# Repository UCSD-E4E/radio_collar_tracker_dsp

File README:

radio_collar_tracker_drone
====================
Airborne Wildlife Radio Collar Tracker - UAS Component

Engineers for Exploration, UCSD Project

Installing the payload software
===============================
1.	Install the required dependencies
	1.	python
	2.	pynmea2
		1.	`pip install pynmea2`
	3.  pyserial
		1.  `sudo apt-get install python-serial`
	4.	libusb-1.0-0-dev
	3.	rtl-sdr
		1.	`git clone https://github.com/steve-m/librtlsdr`
		2.	`mkdir librtlsdr/build`
		3.	`cd librtlsddr/build`
		4.	`sudo cmake ../ -DINSTALL_UDEV_RULES=ON -DDETACH_KERNEL_DRIVER=ON`
		5.	`make`
		6.	`sudo make install`
		7.	`ldconfig`
2.	Install the software
	1.	`cd <radio_collar_tracker_drone>`
	2.  `./autogen.sh`
	3.  `./configure`
	4.	`make`
	5.	`sudo make install`

Running the payload software (standalone)
=========================================
`rctstart`

#Running the payload software (hardware-based initialization)
##Payload Power On Procedure
1.	Disconnect power to AUTOPILOT, PAYLOD
2.	Connect power to PAYLOAD
3.	Connect power to AUTOPILOT
4.	Flip PAYLOAD SWITCH to the ON position.
5.	Wait for the PAYLOAD STATUS LIGHT to turn green for at least 10 seconds.
6.	Flip PAYLOAD SWITCH to the OFF position.
7.	Wait for the PAYLOAD STATUS LIGHT to turn off within 5 seconds.
8.	Connect the GROUND CONTROL STATION to the AUTOPILOT.
9.	Payload Power On Procedure complete.

## Payload Start Procedure
1.	Complete the Payload Power On Procedure.
2.	Flip PAYLOAD SWITCH to the ON position.
3.	Wait for the PAYLOAD STATUS LIGHT to turn green for at least 10 seconds.
4.	Payload Start Procedure complete.

## Payload Stop Procedure
1.	Flip PAYLOAD SWITCH to the OFF position.
2.	Wait for the PAYLOAD STATUS LIGHT to turn off within 5 seconds.
3.	Payload Stop Procedure complete.

## Payload Power Off Procedure
1.	Complete the Payload Stop Procedure.
2.	Disconnect power to the PAYLOAD.
3.	Payload Power Off Procedure complete.

Output Data Format
==================
Output data is located in `/home/pi/rct/`.  Each run consists of a number of IQ
(raw) data files, GPS data files, and a metadata file.  The name format for each
type of file is `[type]_[run]_[file_num]`.  The `type` field specifies, in
capital letters, the type of file (i.e. RAW_DATA, GPS, or META).  The `run`
field specifies a numerical identifier for each run, assigned sequentially.
This field is always 6 characters wide, zero padded.  The `file_num` field
specifies the ordering of the IQ data files.  The first file recorded would have
a file number of 1, sequential files having sequential numbers.  This field is
always 6 characters wide, zero padded.

The raw data files contain the raw IQ data recorded as pairs of 8-bit unsigned
integers.  Each pair represents the in-phase and quadrature components of the
recorded signal in sequence.  See
https://en.wikipedia.org/wiki/In-phase_and_quadrature_components for an
explanation of IQ signal representation.  Each file contains at most 10485760
samples, or 5.12 seconds of data.  IQ data is recorded at 2.048 MSps.

The GPS data files contain timestamped snapshots of autopilot telemetry.  Fields
are comma separated, and are: local capture time (UTC in seconds), lat (degrees
\* 1e7), lon (degrees * 1e7), time since autopilot boot (ms), absolute altitude
(meters MSL), relative altitude (meters AGL), x axis velocity (m/s), y axis
velocity (m/s), z axis velocity (m/s), heading (degrees).  Note: I do not know
whether the heading is relative to true north or magnetic north.  The NED frame
ideally is relative to true north, but I don't know if the heading is reported
before or after declination offsets are taken into account.

The metadata file contains metadata pertaining to the configuration of the
payload.  Each line contains one field.  The key for each field is followed by a
colon, then the value for that field, followed by a newline character:
```
[field_name]: [field_value]
```
The whitespace between the colon and field value is optional, and preferred for
readability, but cannot be a newline.  The metadata file contains the following
fields: local IQ data start time (UTC in seconds), SDR center frequency (Hz),
SDR sampling frequency (Hz), SDR gain (dB).

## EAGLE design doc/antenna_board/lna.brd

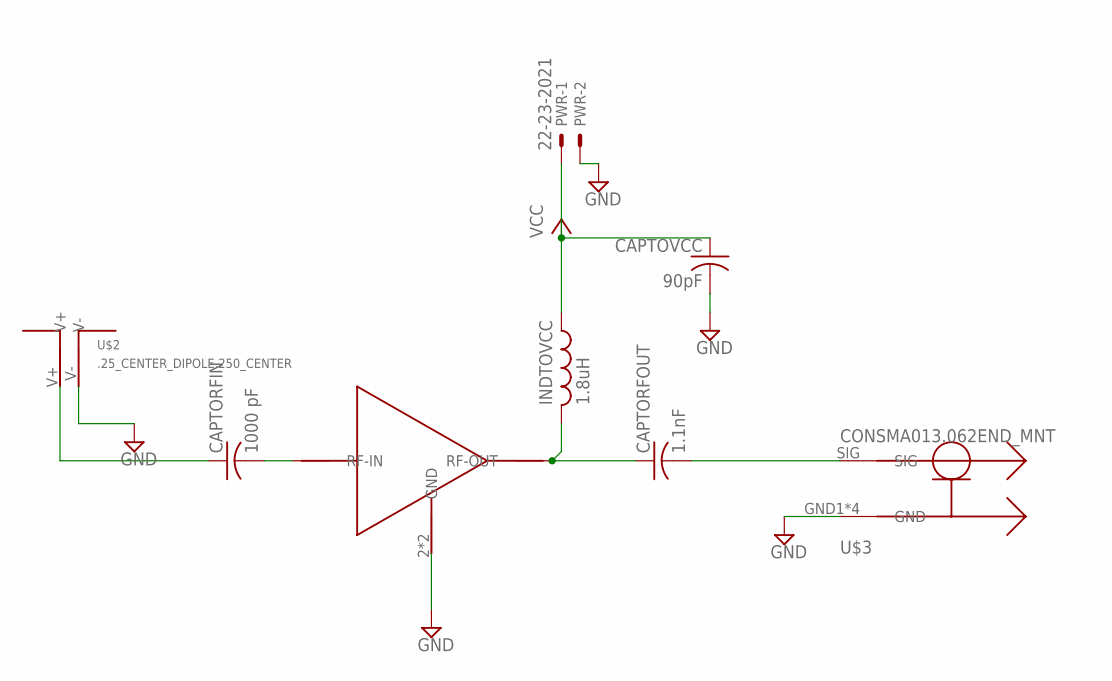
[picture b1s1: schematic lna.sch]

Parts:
CAPTORFIN: 1000 pF; C0603
CAPTORFOUT: 1.1nF; C0603
CAPTOVCC: 90pF; C0603
INDTOVCC: 1.8uH; L2012C
PWR: 22-23-2021
U$1: PSA4-5043+
U$2: .25_CENTER_DIPOLE.250_CENTER; .25_SPACING
U$3: CONSMA013.062END_MNT; SMA_EDGE_MNT

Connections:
GND: CAPTOVCC.2, PWR.2, U$1.2 (GND), U$1.4 (GND), U$2.V-, U$3.GND1 (GND), U$3.GND2 (GND), U$3.GND3 (GND), U$3.GND4 (GND)
unnamed: CAPTORFIN.1, U$2.V+
unnamed: CAPTORFOUT.1, INDTOVCC.2, U$1.1 (RF-OUT)
unnamed: CAPTORFOUT.2, U$3.SIG
unnamed: CAPTORFIN.2, U$1.3 (RF-IN)
VCC: CAPTOVCC.1, INDTOVCC.1, PWR.1

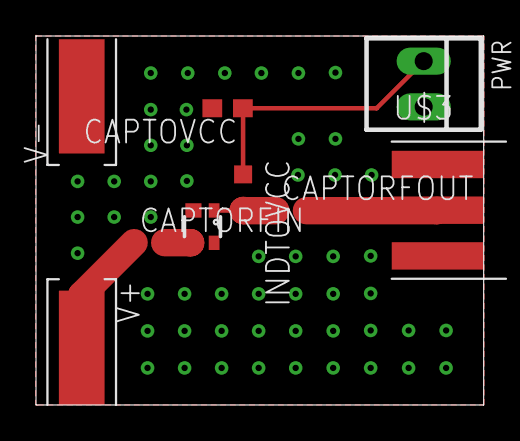
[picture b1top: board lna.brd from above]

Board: 2 copper layers, 24.9 x 20.5 mm, 8 parts (0 on the bottom side), 6 nets.

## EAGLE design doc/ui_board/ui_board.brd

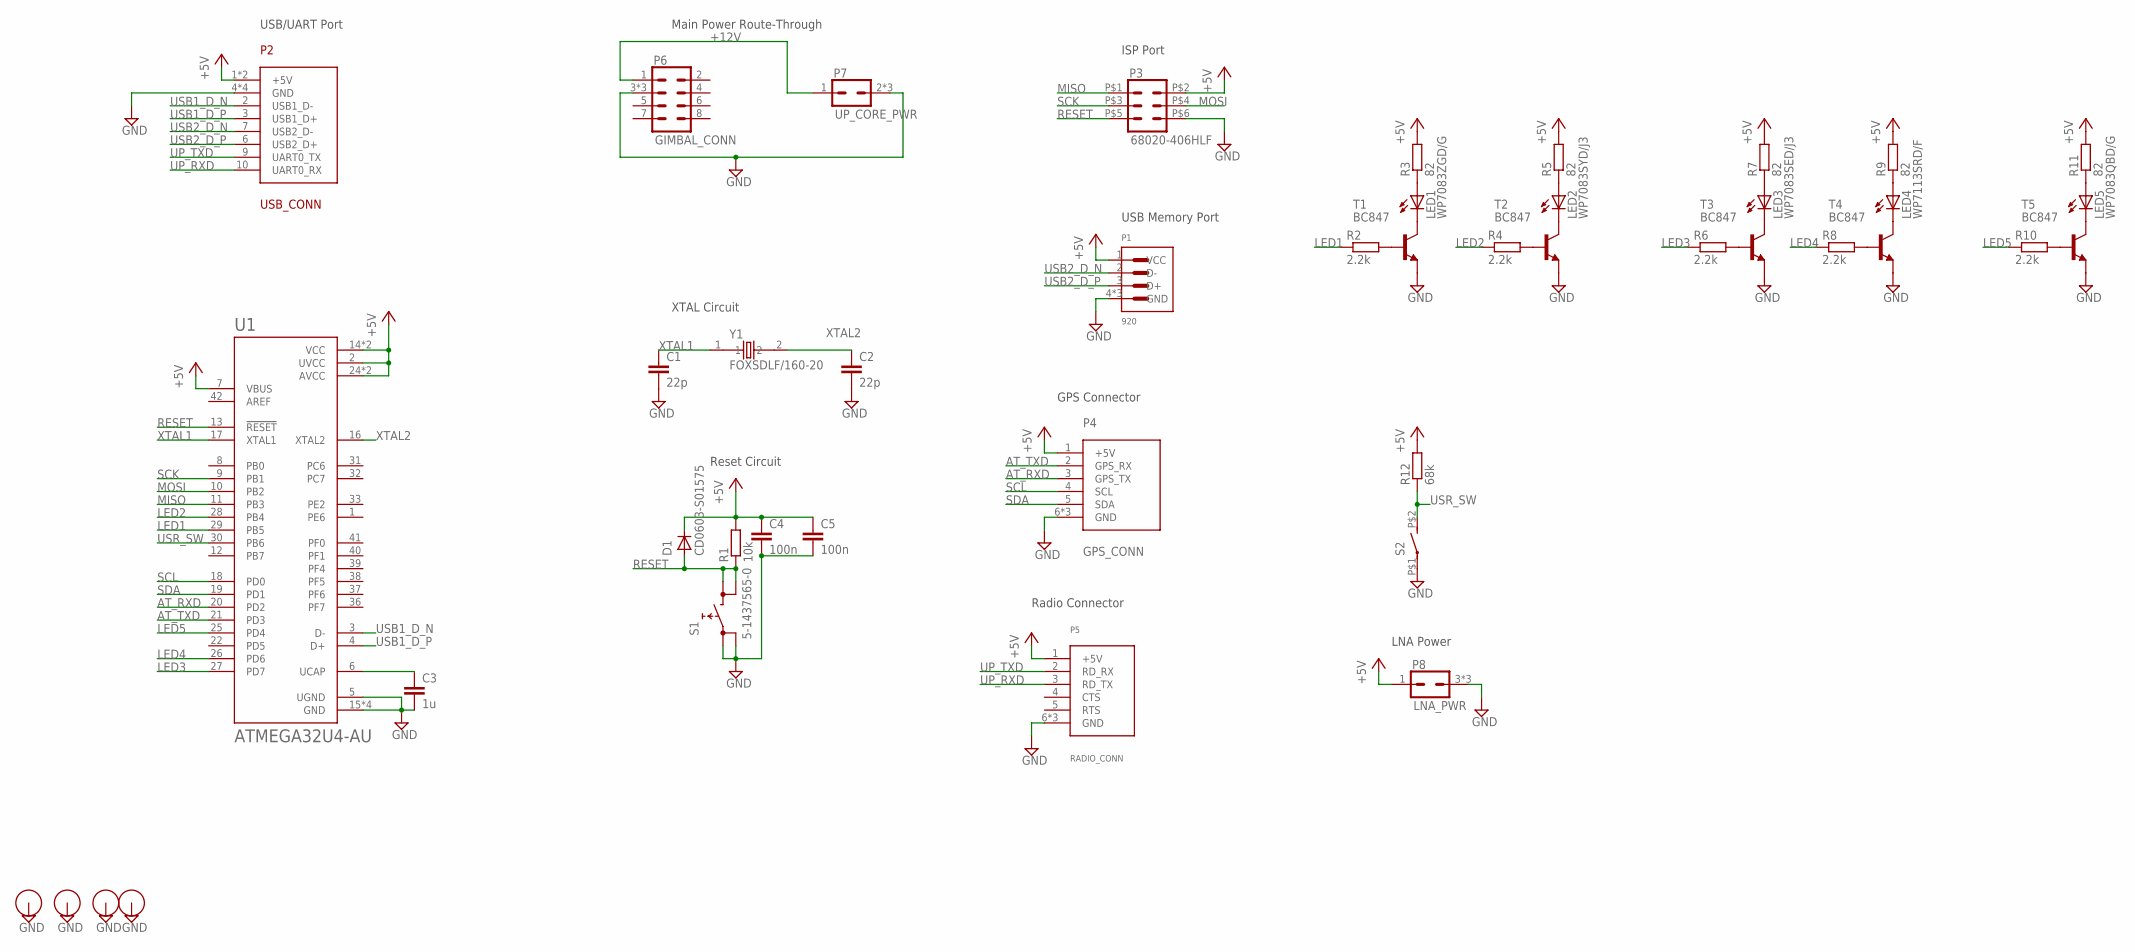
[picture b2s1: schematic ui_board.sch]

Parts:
C1, C2: 22p; C0805
C3: 1u; C0805
C4, C5: 100n; C0805
D1: CD0603-S01575; D0603
LED1: WP7083ZGD/G; LED5MM
LED2: WP7083SYD/J3; LED5MM
LED3: WP7083SED/J3; LED5MM
LED4: WP7113SRD/F; LED5MM
LED5: WP7083QBD/G; LED5MM
P1: 920; USB_THRU
P2: USB_CONN; SM10B-SRSS-TB
P3: 68020-406HLF; 2X3_THRU
P4: GPS_CONN; SM06B-GHS-TB
P5: RADIO_CONN; DF13C-6P-1.25V
P6: GIMBAL_CONN
P7: UP_CORE_PWR; SM02B-GHS-TB
P8: LNA_PWR; SM03B-GHS-TB
R1: 10k; R0805
R2, R4, R6, R8, R10: 2.2k; R0805
R3, R5, R7, R9, R11: 82; R0805
R12: 68k; R0805
S1: 5-1437565-0
S2: 2267078-1
T1, T2, T3, T4, T5: BC847; SOT23
U1: ATMEGA32U4-AU; QFP80P1200X1200X120-44N
U$1, U$3, U$4, U$5: MOUNT_PAD
Y1: FOXSDLF/160-20; XTAL1170X500X450

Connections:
+5V: C4.1, C5.1, D1.P$1 (C), P1.1 (VCC), P2.1 (+5V), P2.5 (+5V), P3.P$2 (2), P4.1 (+5V), P5.1 (+5V), P8.1, R1.2, R3.2, R5.2, R7.2, R9.2, R11.2, R12.2, U1.2 (UVCC), U1.7 (VBUS), U1.14 (VCC), U1.24 (AVCC), U1.34 (VCC), U1.44 (AVCC)
+12V: P6.1, P7.1
AT_RXD: P4.3 (GPS_TX), U1.20 (PD2)
AT_TXD: P4.2 (GPS_RX), U1.21 (PD3)
GND: C1.2, C2.2, C3.2, C4.2, C5.2, P1.4 (GND), P1.5 (GND), P1.6 (GND), P2.4 (GND), P2.8 (GND), P2.G1 (GND), P2.G2 (GND), P3.P$6 (6), P4.6 (GND), P4.G1 (GND), P4.G2 (GND), P5.6 (GND), P5.G1 (GND), P5.G2 (GND), P6.3, P6.GND@1 (3), P6.GND@2 (3), P7.2, P7.G1 (2), P7.G2 (2), P8.3 (2), P8.G1 (2), P8.G2 (2), S1.P$1 (0), S1.P$2 (0), S2.P$1, T1.2 (E), T2.2 (E), T3.2 (E), T4.2 (E), T5.2 (E), U1.5 (UGND), U1.15 (GND), U1.23 (GND), U1.35 (GND), U1.43 (GND), U$1.P$1, U$3.P$1, U$4.P$1, U$5.P$1
LED1: R2.1, U1.29 (PB5)
LED2: R4.1, U1.28 (PB4)
LED3: R6.1, U1.27 (PD7)
LED4: R8.1, U1.26 (PD6)
LED5: R10.1, U1.25 (PD4)
MISO: P3.P$1 (1), U1.11 (PB3)
MOSI: P3.P$4 (4), U1.10 (PB2)
unnamed: LED1.K (C), T1.3 (C)
unnamed: C3.1, U1.6 (UCAP)
unnamed: LED2.K (C), T2.3 (C)
unnamed: LED3.K (C), T3.3 (C)
unnamed: LED4.K (C), T4.3 (C)
unnamed: LED5.K (C), T5.3 (C)
unnamed: R2.2, T1.1 (B)
unnamed: LED1.A, R3.1
unnamed: R4.2, T2.1 (B)
unnamed: LED2.A, R5.1
unnamed: R6.2, T3.1 (B)
unnamed: LED3.A, R7.1
unnamed: R8.2, T4.1 (B)
unnamed: LED4.A, R9.1
unnamed: R10.2, T5.1 (B)
unnamed: LED5.A, R11.1
RESET: D1.P$2 (A), P3.P$5 (5), R1.1, S1.P$3 (1), S1.P$4 (1), U1.13 (!RESET)
SCK: P3.P$3 (3), U1.9 (PB1)
SCL: P4.4 (SCL), U1.18 (PD0)
SDA: P4.5 (SDA), U1.19 (PD1)
UP_RXD: P2.10 (UART0_RX), P5.3 (RD_TX)
UP_TXD: P2.9 (UART0_TX), P5.2 (RD_RX)
USB1_D_N: P2.2 (USB1_D-), U1.3 (D-)
USB1_D_P: P2.3 (USB1_D+), U1.4 (D+)
USB2_D_N: P1.2 (D-), P2.7 (USB2_D-)
USB2_D_P: P1.3 (D+), P2.6 (USB2_D+)
USR_SW: R12.1, S2.P$2 (S), U1.30 (PB6)
XTAL1: C1.1, U1.17 (XTAL1), Y1.1
XTAL2: C2.1, U1.16 (XTAL2), Y1.2

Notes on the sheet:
USB/UART Port
Reset Circuit
XTAL Circuit
ISP Port
USB Memory Port
GPS Connector
Radio Connector
Main Power Route-Through
LNA Power

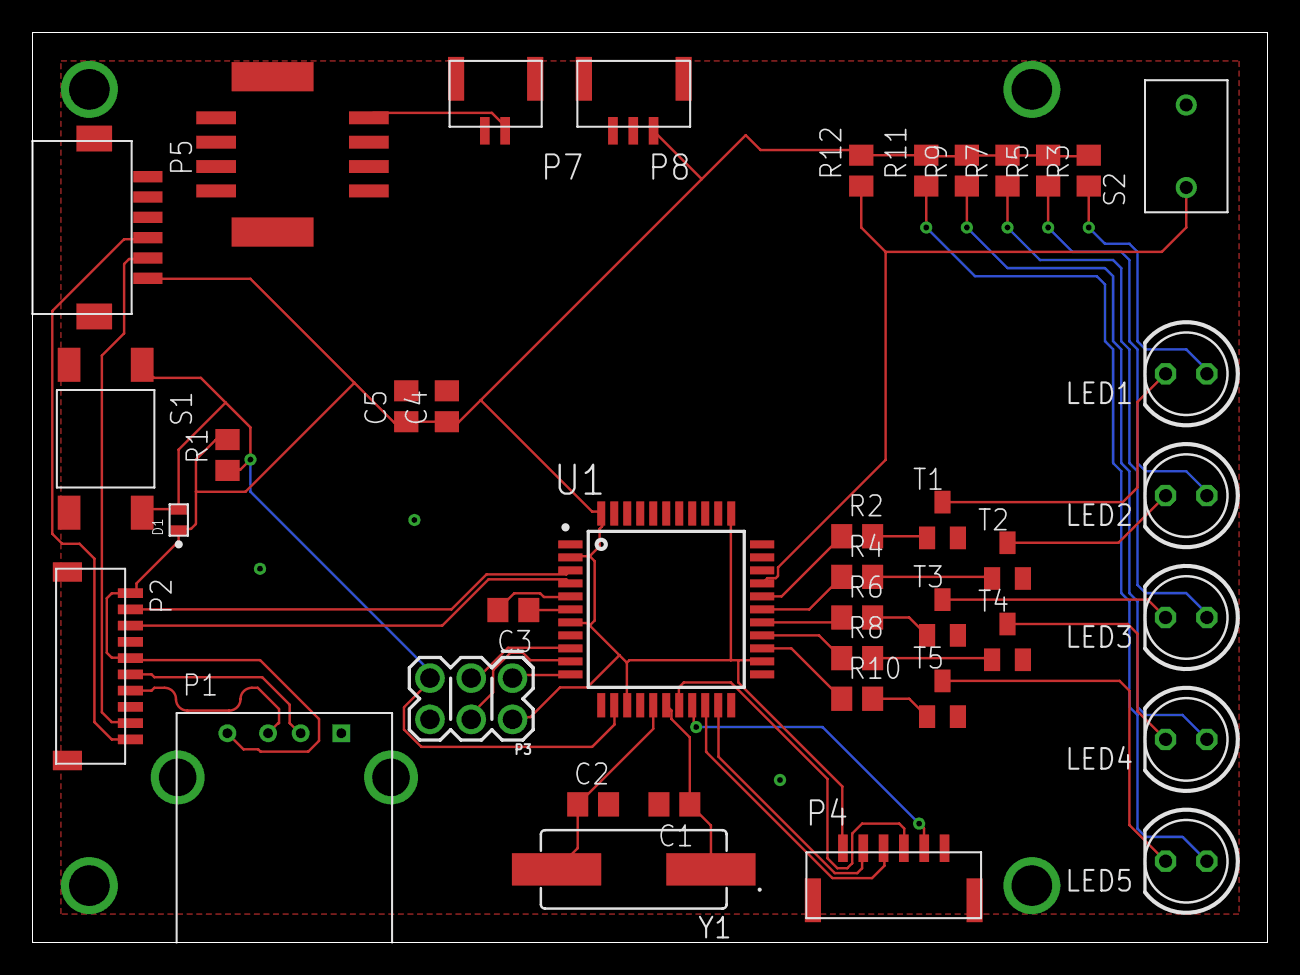
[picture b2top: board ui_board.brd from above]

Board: 2 copper layers, 76.0 x 56.0 mm, 44 parts (0 on the bottom side), 41 nets.

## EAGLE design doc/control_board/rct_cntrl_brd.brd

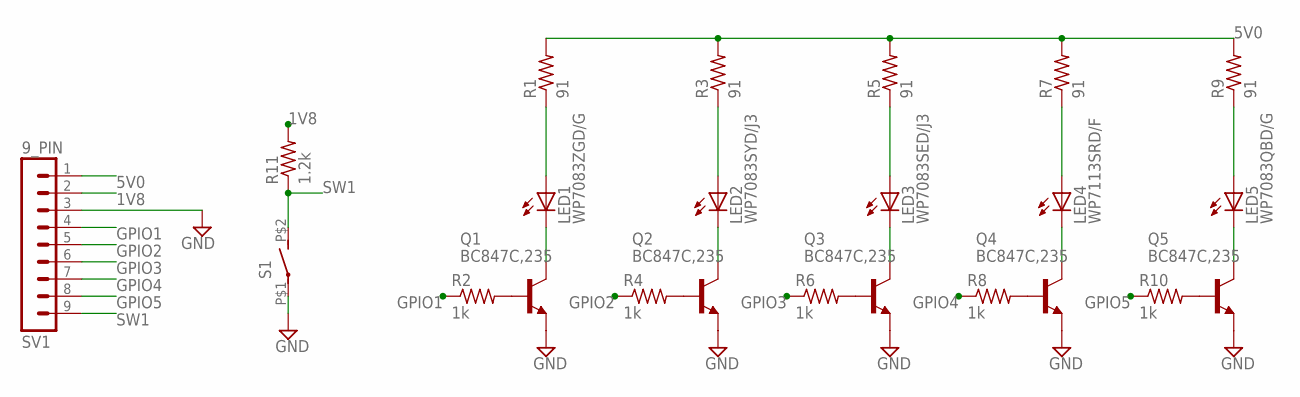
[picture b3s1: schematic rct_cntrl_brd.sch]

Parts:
LED1: WP7083ZGD/G; LED5MM
LED2: WP7083SYD/J3; LED5MM
LED3: WP7083SED/J3; LED5MM
LED4: WP7113SRD/F; LED5MM
LED5: WP7083QBD/G; LED5MM
Q1, Q2, Q3, Q4, Q5: BC847C,235; SOT23-BEC
R1, R3, R5, R7, R9: 91; R0603
R2, R4, R6, R8, R10: 1k; R0603
R11: 1.2k; R0603
S1: TMS6T5B2M2RE; PC_THRU_HOLE_2
SV1: 9_PIN; MA09-1

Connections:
1V8: R11.2, SV1.2
5V0: R1.2, R3.2, R5.2, R7.2, R9.2, SV1.1
GND: Q1.E, Q2.E, Q3.E, Q4.E, Q5.E, S1.P$1, SV1.3
GPIO1: R2.1, SV1.4
GPIO2: R4.1, SV1.5
GPIO3: R6.1, SV1.6
GPIO4: R8.1, SV1.7
GPIO5: R10.1, SV1.8
unnamed: LED3.K (C), Q3.C
unnamed: LED1.A, R1.1
unnamed: LED1.K (C), Q1.C
unnamed: Q1.B, R2.2
unnamed: LED2.A, R3.1
unnamed: LED2.K (C), Q2.C
unnamed: Q2.B, R4.2
unnamed: LED3.A, R5.1
unnamed: Q3.B, R6.2
unnamed: LED4.A, R7.1
unnamed: LED4.K (C), Q4.C
unnamed: Q4.B, R8.2
unnamed: LED5.A, R9.1
unnamed: LED5.K (C), Q5.C
unnamed: Q5.B, R10.2
SW1: R11.1, S1.P$2 (S), SV1.9

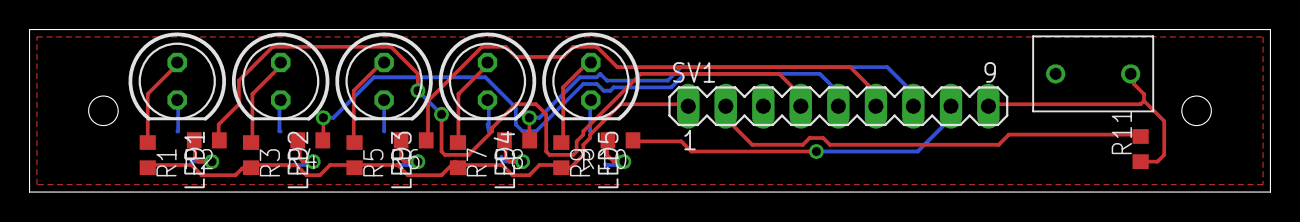
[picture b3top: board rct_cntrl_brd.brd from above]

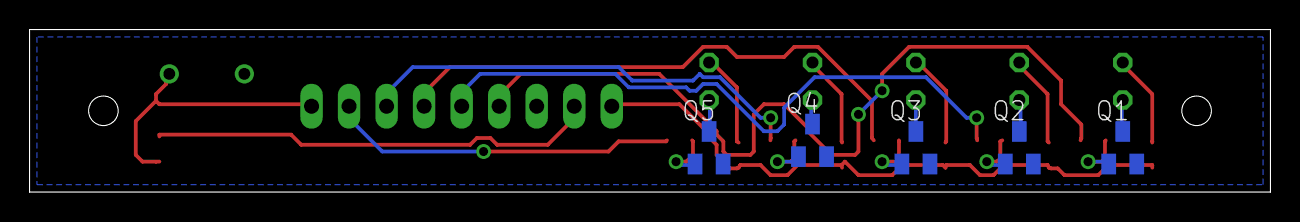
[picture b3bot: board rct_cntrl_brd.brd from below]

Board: 2 copper layers, 84.0 x 11.0 mm, 23 parts (5 on the bottom side), 24 nets.

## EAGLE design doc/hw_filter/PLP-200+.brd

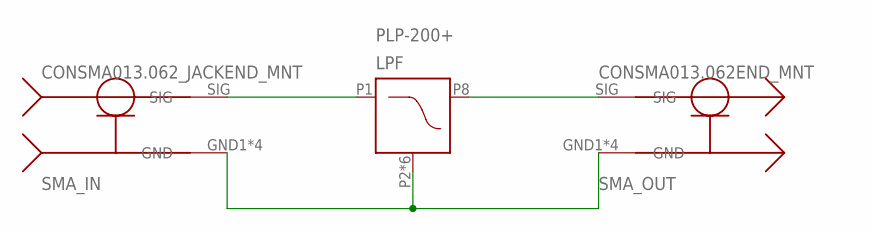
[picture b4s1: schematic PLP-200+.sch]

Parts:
LPF: PLP-200+; A01
SMA_IN: CONSMA013.062_JACKEND_MNT; SMA_EDGE_MNT
SMA_OUT: CONSMA013.062END_MNT; SMA_EDGE_MNT

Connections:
GND: LPF.P2 (GND), LPF.P3 (GND), LPF.P4 (GND), LPF.P5 (GND), LPF.P6 (GND), LPF.P7 (GND), SMA_IN.GND1 (GND), SMA_IN.GND2 (GND), SMA_IN.GND3 (GND), SMA_IN.GND4 (GND), SMA_OUT.GND1 (GND), SMA_OUT.GND2 (GND), SMA_OUT.GND3 (GND), SMA_OUT.GND4 (GND)
unnamed: LPF.P1 (RF_IN), SMA_IN.SIG
unnamed: LPF.P8 (RF_OUT), SMA_OUT.SIG

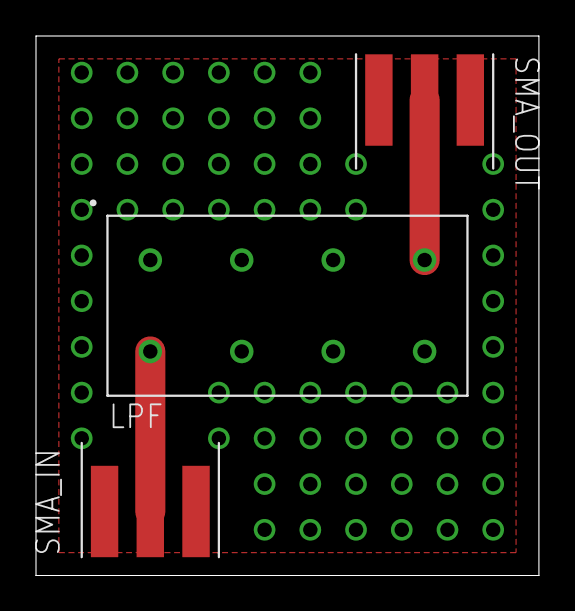
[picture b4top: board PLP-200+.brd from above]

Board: 2 copper layers, 27.9 x 30.0 mm, 3 parts (0 on the bottom side), 3 nets.

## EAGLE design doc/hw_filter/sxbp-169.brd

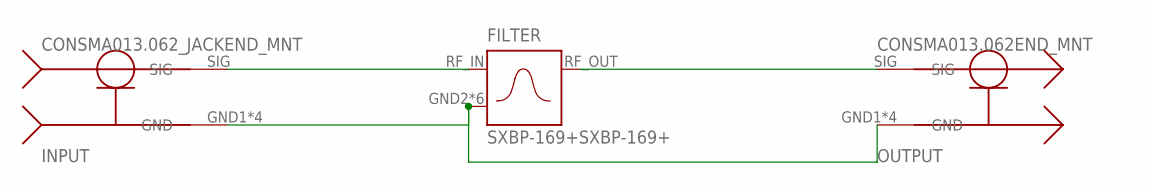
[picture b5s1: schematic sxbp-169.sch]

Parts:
FILTER: SXBP-169+SXBP-169+; HF1139
INPUT: CONSMA013.062_JACKEND_MNT; SMA_EDGE_MNT
OUTPUT: CONSMA013.062END_MNT; SMA_EDGE_MNT

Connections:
GND: FILTER.GND2 (GND_IN), FILTER.GND3 (GND_IN), FILTER.GND4 (GND_IN), FILTER.GND5 (GND_IN), FILTER.GND6 (GND_IN), FILTER.GND7 (GND_IN), INPUT.GND1 (GND), INPUT.GND2 (GND), INPUT.GND3 (GND), INPUT.GND4 (GND), OUTPUT.GND1 (GND), OUTPUT.GND2 (GND), OUTPUT.GND3 (GND), OUTPUT.GND4 (GND)
unnamed: FILTER.RF_IN, INPUT.SIG
unnamed: FILTER.RF_OUT, OUTPUT.SIG

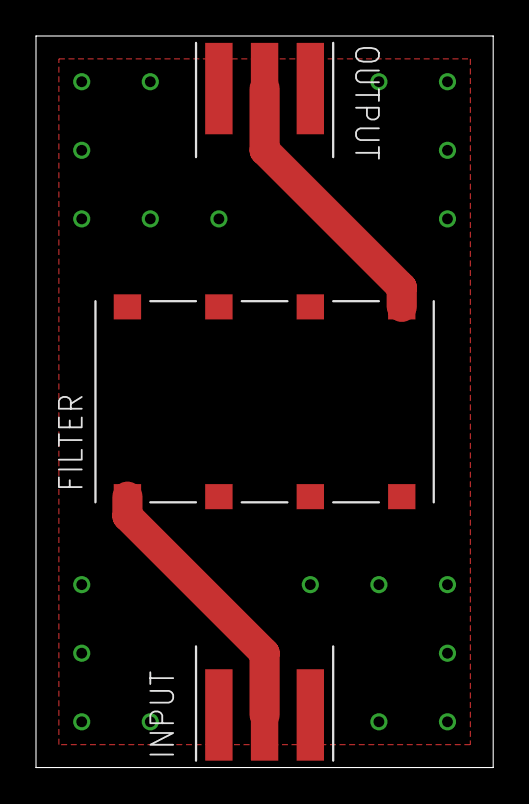
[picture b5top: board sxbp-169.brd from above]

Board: 2 copper layers, 25.4 x 40.6 mm, 3 parts (0 on the bottom side), 3 nets.

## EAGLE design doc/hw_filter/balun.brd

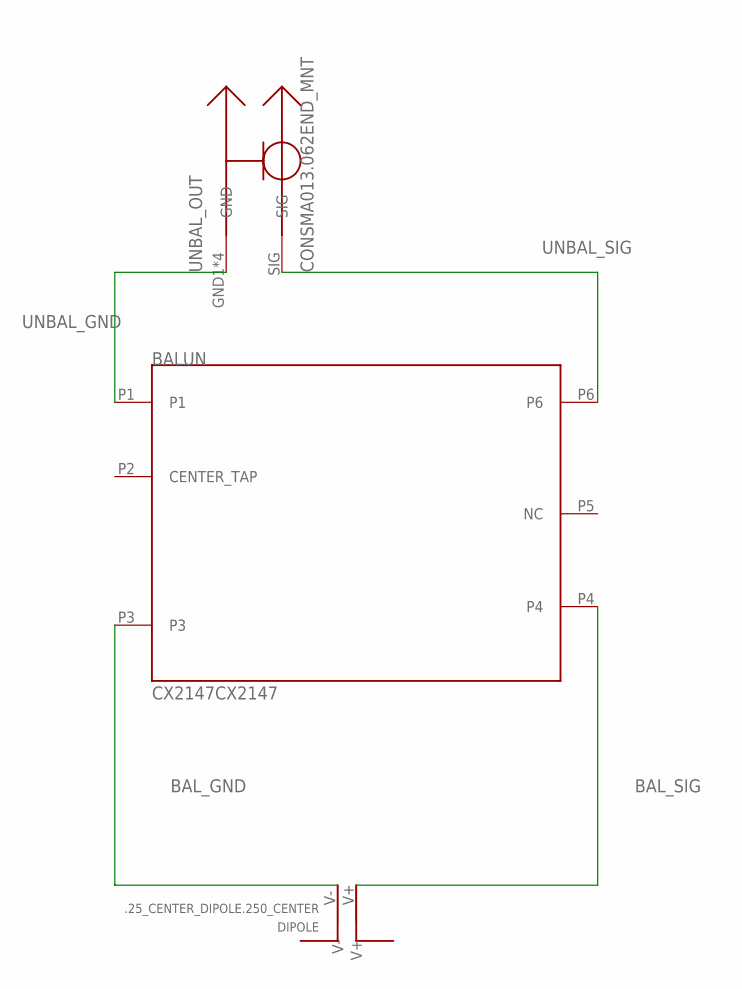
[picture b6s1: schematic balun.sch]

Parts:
BALUN: CX2147CX2147; 6-SMD
DIPOLE: .25_CENTER_DIPOLE.250_CENTER; .25_SPACING
UNBAL_OUT: CONSMA013.062END_MNT; SMA_EDGE_MNT

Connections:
BAL_GND: BALUN.P3, DIPOLE.V-
BAL_SIG: BALUN.P4, DIPOLE.V+
UNBAL_GND: BALUN.P1, UNBAL_OUT.GND1 (GND), UNBAL_OUT.GND2 (GND), UNBAL_OUT.GND3 (GND), UNBAL_OUT.GND4 (GND)
UNBAL_SIG: BALUN.P6, UNBAL_OUT.SIG

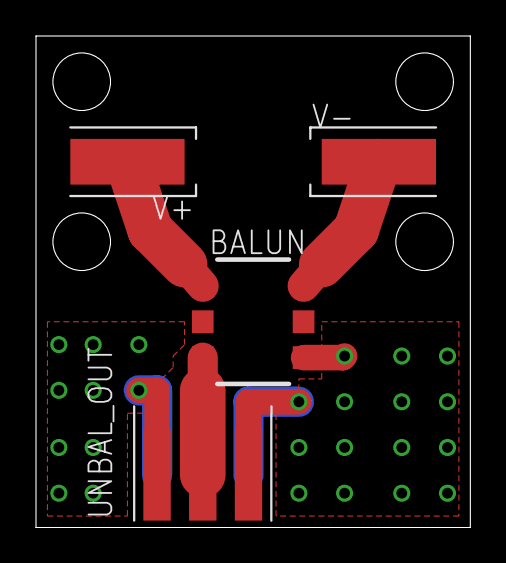
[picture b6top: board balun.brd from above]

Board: 2 copper layers, 24.1 x 27.3 mm, 3 parts (0 on the bottom side), 4 nets.

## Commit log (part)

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2019-03-04 Removed test line
2019-03-06 Removed cJSON submodule
2019-03-06 v0.2 on trm
2019-03-06 Added Arduino 1.5.5-r2 for library reference
2019-03-07 Updated State Tables in TRM, added TRM to commit files
2019-03-07 Changed submodule from ssh to https, updated Makefile to remove cJSON and I2C library paths
2019-03-07 Added Dockerfile for avr build environment
2019-03-13 COnfigured to add fftw
2019-03-13 added local clean rule to remove debugging log files
2019-03-13 Fixed frequency shift configuration
2019-03-13 Fixed docs, added better debugging facilities
2019-03-15 Switched the DSP core over to the energy detector instead of frequency detector
2019-03-15 Added temporary workdir
2019-03-15 Added FIR analysis code
2019-03-31 Updated system diagram
2019-03-31 Reconfigured the dockerfile for dev work
2019-03-31 Updated local build script
2019-04-06 Added LED Status Blinking
2019-04-21 Added multi-target detection and identification
2019-04-21 Removed DSPV1 reference
2019-04-21 Added a run script to launch the Docker image with proper flags
2019-04-21 Added M4 script for ax_boost_program_options
2019-04-21 Validated real-time configuration
2019-04-25 Added link to host devices
2019-04-25 Added mounting for host devices
2019-04-25 Added serial GPS module
2019-04-29 Updated to new comm spec
2019-04-29 Updated dlib flags
2019-05-01 Added install target
2019-05-01 Added double brackets for bash-iness
2019-05-01 OOPified SDR
2019-05-01 Configured test and serial GPS
2019-05-01 Implemented localization and updated ifaces
2019-05-01 Update from dev to implement blinky and size fixes
2019-05-01 Added newline
2019-05-01 Enabled output for testing
2019-05-01 Enabled output for clean end
2019-05-02 Updated boot flags
2019-05-02 Added I2C state bypass
2019-05-03 Added test firmware for HIL testing
2019-05-03 Updated UHD options, set DLIB versions
2019-05-03 Updated dependencies
2019-05-03 Added setStartTime
2019-05-03 Added center frequency
2019-05-03 Fixed stopping issue, fixed GPS timing issue
2019-05-03 integrated GPS and localizer
2019-05-03 Added time output to debug
2019-05-03 Fixed output
2019-05-05 updated gitignore
2019-05-05 Reenabled non-RMC messages
2019-05-05 Updated for new interfaces
2019-05-05 Added Serial receive test
2019-05-05 Added RF signal recording
2019-05-05 Removed extraneous prints
2019-05-05 Added GPS data recording
2019-05-05 Added test for file output, fixed comparison?
2019-05-06 added start time output
2019-05-06 Added wait for test configuration
2019-05-06 Fixed output width
2019-05-06 Fixed test configuration parameters and run config
2019-05-07 Fixed output formatting
2019-05-07 Fixed parameters to reflect different datasets, also modularized fft_len
2019-05-07 Added streaming output
2019-05-07 Changed offline datarate
2019-05-07 Added visualization tool
2019-05-07 Added output flags
2019-05-07 Run script
2019-05-07 removed tcp
2019-05-07 Fixed signal
2019-05-11 Fixed auto stop for test configuration
2019-07-16 Removed dlib
2019-07-16 Updated run script with new data location on UP Core and sampling frequencies
2019-07-16 Updated names
2019-07-16 Removed old DSPV3 modules
2019-07-16 Removed localization header
2019-07-16 Fixed device arguments, added timing checks
2019-07-16 Removed localizer
2019-07-16 Removed old modules, wrote new pipeline with FFT first
2019-07-16 Added debug and power function
2019-07-16 Added python versioned check module
2019-07-16 Fixed m4
2019-07-16 Removed old python dependencies
2019-07-17 Added python3, removed dlib, added tmux
2019-07-17 readded localization
2019-07-17 Removed dlib dependencies
2019-07-17 Added debug catches
2019-07-17 Added frequencies, readded gps and localization
2019-07-17 Added modular ping parameters, fixed args
2019-07-17 Added config file for pings
2019-07-18 Removed old dspv1 core
2019-07-18 Fixed timing, added another test GPS mode
2019-07-18 Removed dspv1, fir, integrator, classifier
2019-07-18 Added debug messages
2019-07-18 Added null core start time, and renamed getPosition to include units
2019-07-18 Removed estimation, added secondary queue
2019-07-18 Added secondary queue
2019-07-18 Added default values
2019-07-18 Added gps mode option, updated DSP time
2019-07-18 Added config file options
2019-07-18 Changed time source, added try catch for parsing block
2019-07-18 Fixed integration constants
2019-07-18 Added debug timing, added wait for new position for future pings
2019-07-19 Added udp client
2019-07-19 Added UDP receiver
2019-07-20 Final fixes to udp_client for functionality
2019-07-20 Moved gps_target to config file
2019-07-20 Updated to reflect new args
2019-07-20 Made frequencies a parameter
2019-07-20 Disabled frequency print, optimized GPS buffer code
2019-07-22 Added hearbeat
2019-07-22 Fixed input dir
2019-07-23 Calculates estimate in real time
2019-07-23 Added Precision Analysis Jupyter Notebook
2019-07-25 Finished visualization
2019-07-25 Creates point.kml file if none exists before receiving any pings
2019-07-25 Removed extraneous print messages
2019-07-26 Fixed lat/lon format, and decoding
2019-07-26 Fixed heartbeat packet
2019-07-26 Added flag to prevent overwriting time too many times
2019-07-28 Fixed data store device name
2019-07-28 Fixed formatting
2019-07-28 Moved python scripts to scripts folder
2019-07-28 Moved drone_run script to scripts
2019-07-28 Replaced with rct_config and boost::program_options
2019-07-28 Fixed config script install
2019-07-28 Reorganized GCS software
2019-07-28 Removed sdr_starter for drone_run.py
2019-07-28 Moved pos_estimate to gcs software
2019-07-28 Removed getRunNum.py - obsolete
2019-07-28 Reogranized new autostart scripts
2019-07-28 Removed rct_blink
2019-07-28 Removed parser.sh
2019-07-29 Removed gps_logger automake, removed extra python check
2019-07-29 Updated scripts Makefile
2019-07-29 Changed automount to /etc/fstab
2019-07-29 Removed trailing spaces, added gps_baud rate, added output directory
2019-07-29 Fixed inaccurate flag
2019-07-29 Added wait for hearbeat
2019-07-29 Added CommandGateway module
2019-07-29 Added udp client simulator
2019-07-29 Added compile and support clients
2019-07-29 Added Python start script opts
2019-07-29 switched to python3, added command GUI
2019-07-29 Added UDP COmmand listener
2019-07-29 Added Python opts to ignore
2019-07-29 Removed 3dr and trm manuals
2019-07-29 Fixed cmdListener
2019-07-29 Half fixed close issue
2019-07-29 added select
2019-07-29 Aded setRun
2019-07-31 Wrapped into class
2019-07-31 Removed extraneous script
2019-07-31 reformatted rct_config
2019-07-31 Added execute flag
2019-07-31 Removed extraneous script - folded into commander
2019-07-31 Reformatted target_bin expression
2019-07-31 switching to default python
2019-07-31 switched to python3 tkinter
2019-07-31 Fixed multiple fstab entries
2019-07-31 Fixed option to wildcard for delete
2019-07-31 Fixed sed regex
2019-07-31 added autostart flag
2019-07-31 Hardcoded python
2019-07-31 Fixed autostart flag, status serialization
2019-07-31 Added heartbeat watchdog
2019-07-31 Fixed status message
2019-07-31 Added datetime
2019-07-31 Fixed command packet
2019-07-31 Fixed packet
2019-07-31 Added freq gui
2019-07-31 Set freq test
2019-07-31 Fixed commandGateway freqs reference
2019-07-31 Fixed freqElements update
2019-07-31 Fixed entry end
2019-07-31 Fixed setF packet
2019-07-31 Fixed freqs
2019-07-31 Added response
2019-08-01 Fixed multi-transmitter display
2019-08-03 Added functionality on Windows machines
2019-08-03 Added initial configuration window
2019-08-03 Added comma
2019-08-03 Updated rct_config
2019-08-03 Fixed stupid multi transmitter failures, added better visualizations
2019-08-03 Fixed test simulator for multiple transmitters
2019-08-04 Fixed options packet
2019-08-04 Added setOptions
2019-08-04 Added print
2019-08-04 Initial remote upgrade feature commit
2019-08-04 Added socket fixes
2019-08-04 Fixed sockets
2019-08-04 Fixed sockets?
2019-08-04 Added auto restart
2019-08-04 Added socket retry
2019-08-04 Fixed connect tries
2019-08-04 Added upgrade error checking
2019-08-04 Moved to python3
2019-08-04 Added binary bits
2019-08-04 Fixed lack of upgrade status
2019-08-06 Added loggint
2019-08-06 Added print e for serial fail
2019-08-06 Added domain checking for log
2019-08-06 Added GPS state check
2019-08-07 Added minSNR to options
2019-08-07 Added logging capability
2019-08-07 Fixed logging
2019-08-07 Updated the minimum SNR
2019-08-07 Added test mode and auto recheck for GPS
2019-08-07 Added boilerplate for no heartbeat notification
2019-08-07 Implemented correctly
2019-08-07 Added unzip
2019-08-07 Added argv
2019-08-07 Fixed upgrade?
2019-08-07 Fixed update and auto restart
2019-08-07 Added valid heartbeat
2019-08-07 Removed extraneous tests
2019-08-07 Updated docs .gitignore to ignore generated tex files and interim files
2019-08-07 Added V2 signal detector system diagram
2019-08-07 Added clean instruction to clean interim files
2019-08-08 Added config param checking and backups
2019-08-08 Added config params readback, options checking
2019-08-08 Fixed ping frequency
2019-08-08 Added exception display
2019-08-27 final commit
2019-08-27 Final Push
2019-10-24 Moved wget and tmux install to start of build
2019-10-24 Removed extraneous class
2019-10-24 Removed extraneous Classifier class
2019-10-24 Removed extraneous FIR class
2019-10-24 Removed extraneous Integrator class
2019-10-24 Ignoring doxygen output
2019-10-24 Renamed Doxyfile
2019-10-25 Added test for Doxygen
2019-10-25 Added Doxygen rules
2019-10-25 Fixed rule for Doxygen
2019-10-25 Changed Doxygen output location and adding m4 macros
2019-10-26 Fixed doxygen options, and gitignore
2019-10-28 Added docstrings to StatusPacket and state enums
2019-11-12 Added docstrings
2019-11-12 Formatted docstrings
2019-11-12 Removed trailing whitespace
2019-11-19 Added docstrings and consts
2019-11-19 Fixed includes and consts
2019-11-19 Added docstrings, added _core check to GPS::stop
2019-11-19 Added docstring for RTT::IQdata::size
2019-11-20 Added docstring to RTT::PingLocalizer
2019-11-20 Added and fixed docstrings to RTT::SDR and RTT::AbstractSDR
2019-11-20 Added docstring for RTT::SDR_RECORD
2019-11-20 Removed unused member
2019-11-20 Marked implemented classes as final
2019-11-20 Added docstrings to RTT::SDR_TEST
2019-11-20 Added docstring for RTT::TimeBlock
2019-11-20 Added todo declaration, and final
2019-11-20 Added file docs
2019-11-20 Fixed shebang
2019-11-22 Removed extraneous python3 packages from docker build
2019-11-22 Added README.md as main page, excluded reset.py
2019-11-22 Updated install instructions
2019-11-22 Unescaped underscores
2019-11-23 Removed references to tagged_signal.hpp
2020-01-07 Added LuaLatex and diagrams as targets
2020-01-07 Added auto vars and pdf2svg
2020-01-07 Ignoring derived svg files
2020-01-07 Eliminated implicit pattern rule
2020-01-26 Updated maintaner-clean
2020-01-26 Forked radio_collar_tracker_uib
2020-01-26 Forked to radio_collar_tracker_gcs
2020-01-26 Remove old test file
2020-02-16 Added payload simulator.py
2020-02-16 Ignoring Eclipse files
2020-04-07 Removed dlib dependency
2020-04-07 removed dlib cppflags
2020-04-07 Fixed GPS not stop in test mode, added config file override
2020-04-07 Initial commit - test configuration
2020-04-07 Updated readme with build instructions
2020-04-08 Implemented initial class structure
2020-04-08 Updated for changed github URLs and branches, added build
2020-04-08 Added instructions for using the docker image
2020-04-13 Fixed fftw instruction, added automake, mako, and numpy dependencies
2020-04-13 Fixed includes
2020-04-18 Added top level controller file - app.py
2020-04-18 Fixed install instructions
2020-04-18 Fixed program options, adjusted formatting
2020-04-18 added more fields in the config file
2020-11-04 Update rctrun.py with CONFIG class
    Adds a CONFIG class to store the values of all the variables from the CONFIG in one instance. Did not yet change every call to `get_var()` to appropriate class calls yet.
2021-01-29 Update rctrun.py
    Updated the tab spacing from earlier
2021-11-04 Updated pipfile
2021-11-05 Updated installation instructions
